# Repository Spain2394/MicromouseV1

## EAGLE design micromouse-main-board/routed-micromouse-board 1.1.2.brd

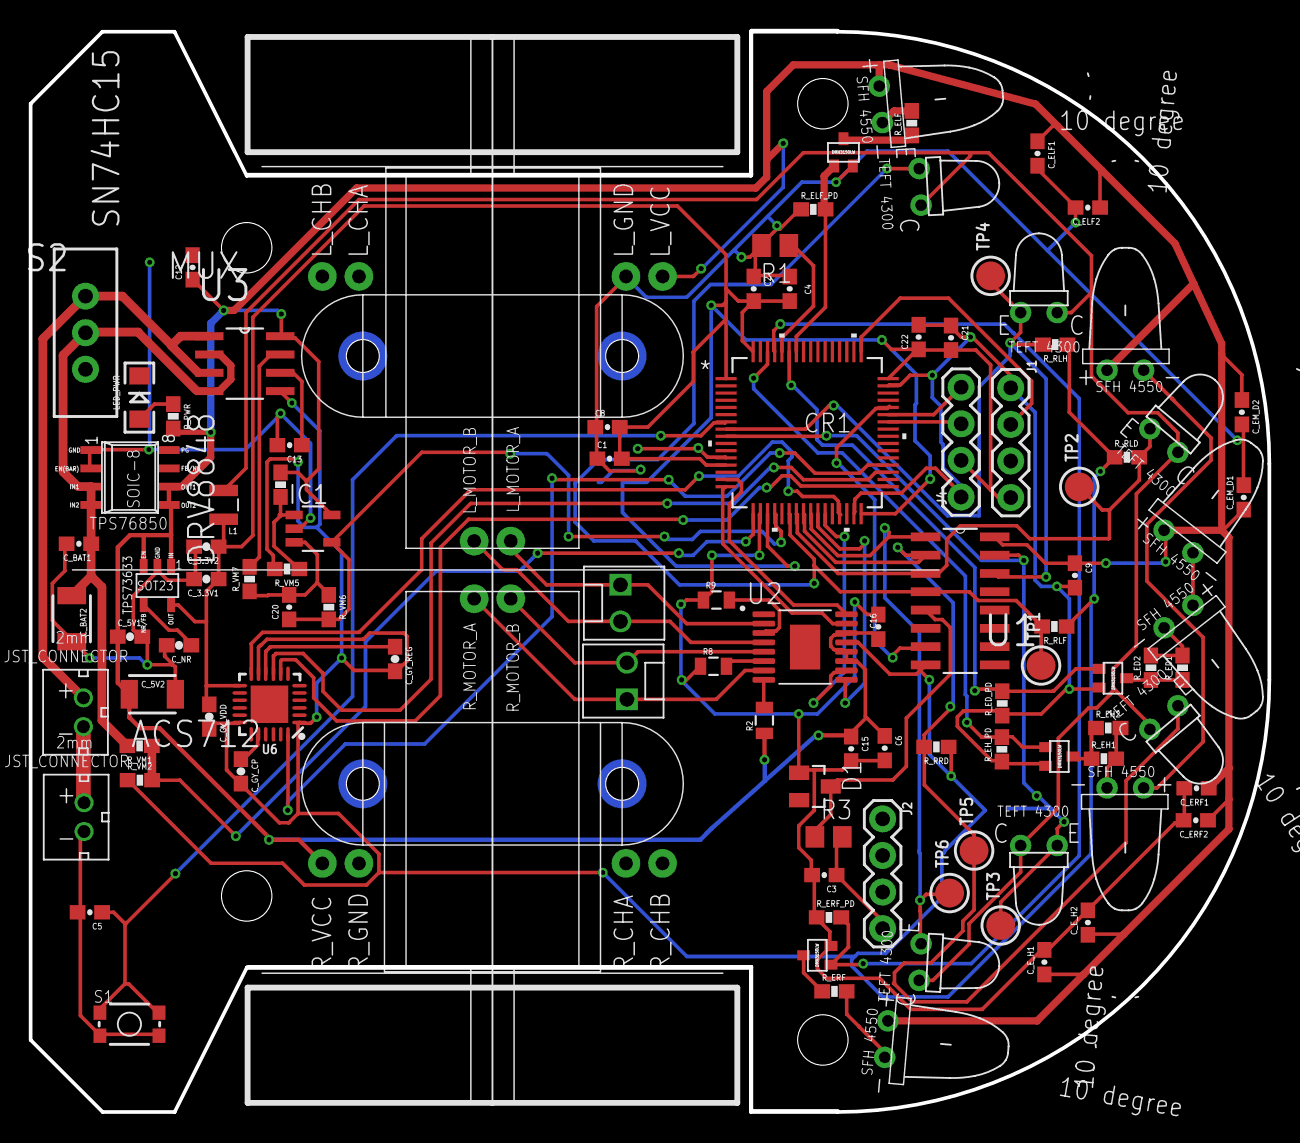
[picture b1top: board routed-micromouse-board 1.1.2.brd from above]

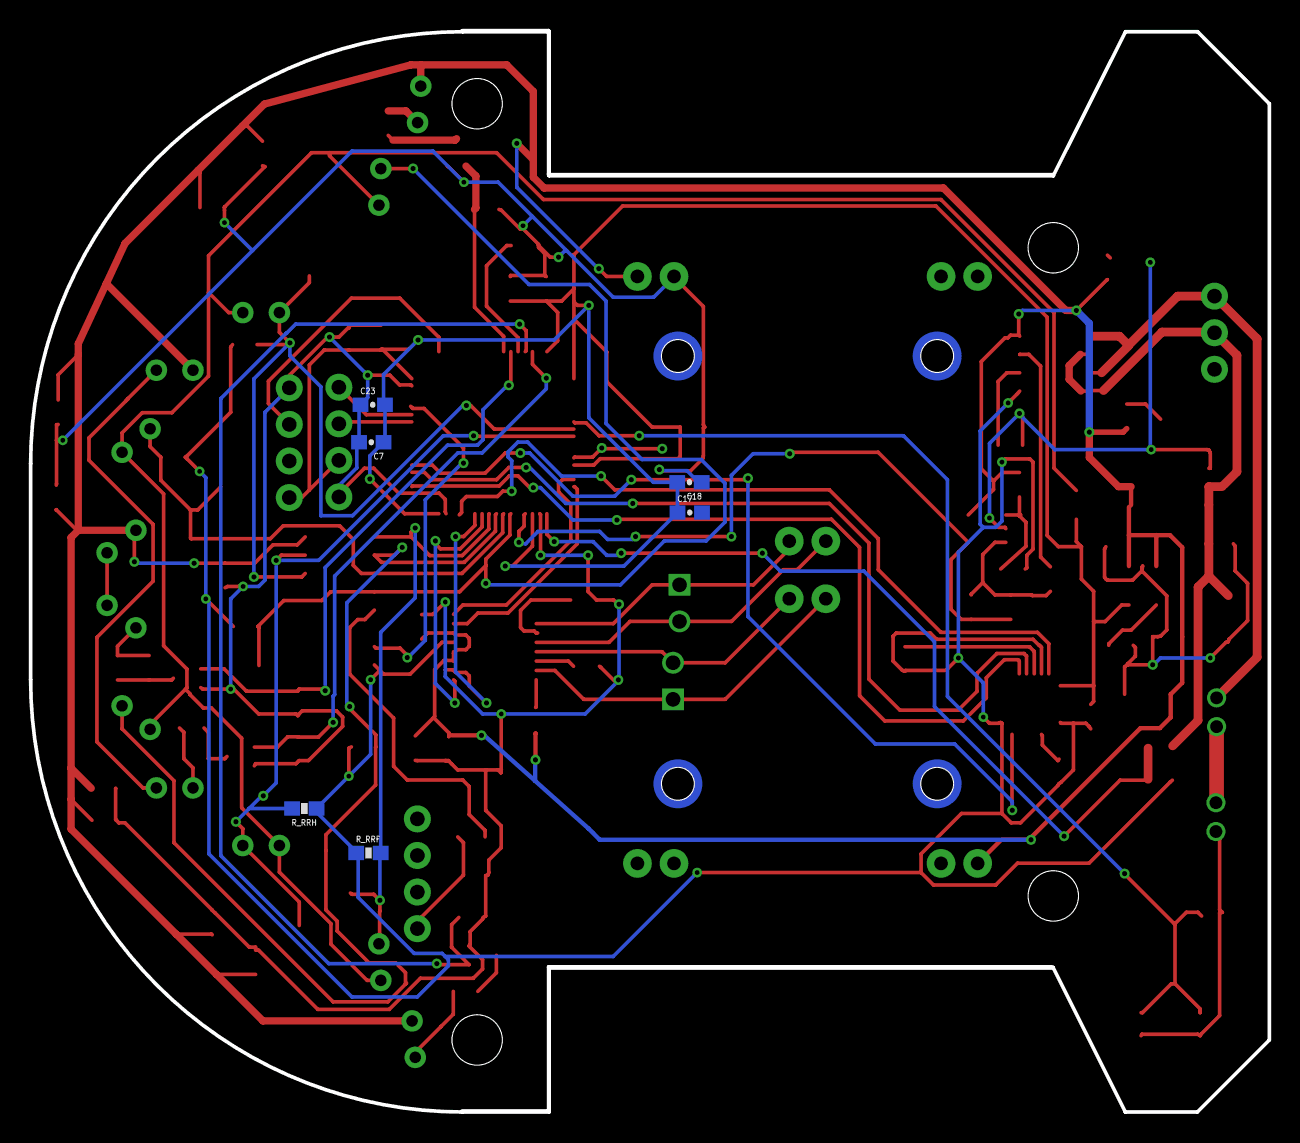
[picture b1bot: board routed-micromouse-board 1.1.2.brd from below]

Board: 2 copper layers, 86.0 x 75.0 mm, 108 parts (6 on the bottom side), 61 nets.

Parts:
C1: 1.1uF; 0603-CAP
C2, C8, C18, C21, C23: 4.7uF; 0603-CAP
C3: 1.4 uF; 0603-CAP
C4, C13: 0.01uF; 0603-CAP
C5, C6, C7, C17, C22: 0.1uF; 0603-CAP
C9, C16: 2.2uF; 0603-CAP
C12: 0.1 uF; 0603-CAP
C15: 10uF; 0603-CAP
C20: 1000pF; 0603-CAP
CR1: STM32F103RET6; LQFP-64
C_3.3V1: 10uF; 0603-CAP
C_3.3V2, C_5V1: 0.1uF; 0603-CAP
C_5V2: 47uF; 1210
C_BAT1: 0.1uF; 0603-CAP
C_BAT2: 47uF; 1210
C_ELF1: 4.7uF; 0603-CAP
C_ELF2: 0.1uF; 0603-CAP
C_EM_D1: 4.7uF; 0603-CAP
C_EM_D2: 0.1uF; 0603-CAP
C_ERF1: 4.7uF; 0603-CAP
C_ERF2: 0.1uF; 0603-CAP
C_E_H1: 4.7uF; 0603-CAP
C_E_H2: 0.1uF; 0603-CAP
C_GY_CP: 2.2nF; 0603-CAP
C_GY_REG: 0.1uF; 0603-CAP
C_GY_VDD: 0.1uF; 0603-CAP
C_NR: 0.1uF; 0603-CAP
D1: SOT23
IC1: LM321MFX; SOT23-5
J1, J2, J4: 1X04
JP1, JP3: MOLEX-1X2
L1: 10uH; 1007
LED_PWR: green; LED-1206
LEFT_FRONT_EMITTER: EMITTER
NMOS1, NMOS2, NMOS3, NMOS4: DMN3150LW
R1: 1k; M0805
R2: 10k; 0805
R3: 1k; R0805
R8, R9: 500m; 0805
REC_LF: RECEIVER
R_ED1, R_ED2: 5.6; 0603-RES
R_ED_PD: 47k; 0603-RES
R_EH1, R_EH2: 5.6; 0603-RES
R_EH_PD: 47k; 0603-RES
R_ELF: 10; 0603-RES
R_ELF_PD: 47k; 0603-RES
R_ERF: 10; 0603-RES
R_ERF_PD: 47k; 0603-RES
R_PWR: 1k; 0603-RES
R_RLD: 1.8k; 0603-RES
R_RLF: 1.8k; 0603-RES
R_RLH: 1.8k; 0603-RES
R_RRD: 1.8k; 0603-RES
R_RRF: 1.8k; 0603-RES
R_RRH: 1.8k; 0603-RES
R_VM1: 75k; 0603-RES
R_VM2: 25k; 0603-RES
R_VM4, R_VM5: 100k; 0603-RES
R_VM6: 3.3k; 0603-RES
R_VM7: 1k; 0603-RES
S1: RESET; TACTILE_SWITCH_SMD_4.6X2.8MM
S2: SWITCH-SPDT
TP1, TP2, TP3, TP4, TP5, TP6: TESTPOINT_ROUND_2MM
U1: SN74HC151DR; SOIC127P600X175-16N
U2: DRV8848PWPR; SOP65P640X120-17N
U3: ACS712ELCTR-20A-T; SOIC127P600X175-8N
U6: MPU-6000; QFN-24-EP
U$1, U$2: JST_CONNECTOR_FEMALE
U$3: TPS73633(SOT-23)
U$4: TPS76850(SOIC-8)
U$7, U$8, U$9, U$20, U$21: RECEIVER
U$11, U$13, U$17, U$18, U$19: EMITTER
U$12: MY_MM_MOTOR_MOUNT

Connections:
3.3V: C1.2, C2.2, C4.2, C7.1, C8.2, C17.1, C18.2, C21.2, C22.1, C23.2, CR1.1, CR1.13, CR1.19, CR1.32, CR1.48, CR1.64, C_3.3V1.1, C_3.3V2.1, C_GY_VDD.1, J1.4, J4.2, L1.1, U6.13, U$3.OUT
5V: C6.1, C9.1, C12.1, C15.1, C16.1, C_5V1.1, C_5V2.1, C_ELF1.1, C_ELF2.1, C_EM_D1.1, C_EM_D2.1, C_ERF1.1, C_ERF2.1, C_E_H1.1, C_E_H2.1, IC1.5, LEFT_FRONT_EMITTER.+, R2.1, R_PWR.2, R_VM4.1, U1.16, U2.11, U2.12, U2.14, U3.8, U$3.EN, U$3.IN, U$4.OUT1, U$4.OUT2, U$11.+, U$12.L_VCC, U$12.R_VCC, U$13.+, U$18.+
(USART1)_RX: CR1.42, J4.3
(USART1)_TX: CR1.43, J4.4
A3.3V: L1.2, REC_LF.C, U$7.C, U$8.C, U$9.C, U$20.C, U$21.C
AGND: C_GY_CP.2, C_GY_REG.2, C_GY_VDD.2, R_RLD.1, R_RLF.1, R_RLH.1, R_RRD.1, R_RRF.1, R_RRH.1, R_VM2.1, R_VM5.2, U1.8, U2.13, U3.5, U6.1, U6.11, U6.18
BATT_CONN: U$1.+, U$2.-
CURRENT_SENSE: C20.1, CR1.20, IC1.4, R_VM6.2
D2_EM: R_ED1.2, R_ED2.2, U$17.-
D_EM: U$11.-, U$17.+
EM_D: CR1.59, NMOS2.G, R_ED_PD.2
EM_H: CR1.62, NMOS4.G, R_EH_PD.2
EM_LF: CR1.58, NMOS1.G, R_ELF_PD.2
EM_RF: CR1.61, NMOS3.G, R_ERF_PD.2
GND: C1.1, C2.1, C3.2, C4.1, C5.2, C6.2, C7.2, C8.1, C9.2, C12.2, C13.2, C15.2, C16.2, C17.2, C18.1, C21.1, C22.2, C23.1, CR1.12, CR1.18, CR1.31, CR1.47, CR1.63, C_3.3V1.2, C_3.3V2.2, C_5V1.2, C_5V2.2, C_BAT1.2, C_BAT2.2, C_ELF1.2, C_ELF2.2, C_EM_D1.2, C_EM_D2.2, C_ERF1.2, C_ERF2.2, C_E_H1.2, C_E_H2.2, C_NR.2, D1.1, IC1.2, J1.1, J4.1, LED_PWR.C, NMOS1.S, NMOS2.S, NMOS3.S, NMOS4.S, R1.2, R8.1, R9.1, R_ED_PD.1, R_EH_PD.1, R_ELF_PD.1, R_ERF_PD.1, S1.1, S1.2, U$1.-, U$3.GND, U$4.EN(BAR), U$4.GND, U$12.L_GND, U$12.R_GND
H2_EM: R_EH1.2, R_EH2.2, U$19.-
H_EM: U$18.-, U$19.+
INT: CR1.29, U6.12
LEFT_MOTOR_H: JP1.1, U2.2, U$12.L_MOTOR_A
LEFT_MOTOR_L: JP1.2, U2.4, U$12.L_MOTOR_B
LF_EM: LEFT_FRONT_EMITTER.-, R_ELF.2
MUX_EN: CR1.44, U1.7
unnamed: C13.1, U3.6
unnamed: D1.3, R3.1, U1.5
unnamed: NMOS3.D, R_ERF.1
unnamed: NMOS1.D, R_ELF.1
unnamed: CR1.60, R1.1
unnamed: R2.2, U2.8
unnamed: R9.2, U2.3
unnamed: NMOS2.D, R_ED1.1, R_ED2.1
unnamed: NMOS4.D, R_EH1.1, R_EH2.1
unnamed: R8.2, U2.6
unnamed: IC1.1, R_VM4.2, R_VM5.1
unnamed: R_VM7.2, U3.7
unnamed: C_NR.1, U$3.NR/FB
unnamed: LED_PWR.A, R_PWR.1
unnamed: C_GY_REG.1, U6.10
unnamed: C_GY_CP.1, U6.20
unnamed: C20.2, IC1.3, R_VM6.1, R_VM7.1
NRST: C5.1, CR1.7, S1.3, S1.4
PWM_MOTOR_1: CR1.15, U2.16
PWM_MOTOR_2: CR1.16, U2.15
PWM_MOTOR_3: CR1.26, U2.9
PWM_MOTOR_4: CR1.27, U2.10
REC_LD: CR1.23, R_RLD.2, TP2.P$1, U1.3, U$7.E
REC_LF: CR1.22, REC_LF.E, R_RLF.2, TP1.P$1, U1.4
REC_LH: CR1.8, R_RLH.2, TP4.P$1, U1.14, U$21.E
REC_RD: CR1.24, R_RRD.2, TP5.P$1, U1.2, U$8.E
REC_RF: CR1.25, R_RRF.2, TP6.P$1, U1.1, U$9.E
REC_RH: CR1.9, R_RRH.2, TP3.P$1, U1.15, U$20.E
RF_EM: R_ERF.2, U$13.-
RIGHT_MOTOR_H: JP3.1, U2.7, U$12.R_MOTOR_A
RIGHT_MOTOR_L: JP3.2, U2.5, U$12.R_MOTOR_B
SENSOR_DEBUG: C3.1, J2.4, R3.2
SPI2_MISO: CR1.35, U6.9
SPI2_MOSI: CR1.36, U6.24
SPI2_NSS: CR1.33, U6.8
SWCLK: CR1.49, J1.2
VBAT_SENSE: CR1.17, R_VM1.1, R_VM2.2
V_BATT: C_BAT1.1, C_BAT2.1, R_VM1.2, S2.2, U3.2, U3.4, U$4.IN1, U$4.IN2
V_BATT_POWER: S2.3, U3.1, U3.3, U$2.+

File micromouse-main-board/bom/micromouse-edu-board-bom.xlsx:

Part | Value | Device | Package | Description | AVAILABILITY | DESCRIPTION | MANUFACTURER_PART_NUMBER | MF | MP | PACKAGE | PRICE | PROD_ID | SF_ID | SPICEPREFIX | VENDOR
C1 | 1.1uF | CAP0603-CAP | 0603-CAP | Capacitor
C2 | 4.7uF | CAP0603-CAP | 0603-CAP | Capacitor
C3 | 1.4 uF | CAP0603-CAP | 0603-CAP | Capacitor
C4 | 0.01uF | CAP0603-CAP | 0603-CAP | Capacitor
C5 | 0.1uF | CAP0603-CAP | 0603-CAP | Capacitor
C6 | 0.1uF | CAP0603-CAP | 0603-CAP | Capacitor
C7 | 0.1uF | CAP0603-CAP | 0603-CAP | Capacitor
C8 | 4.7uF | CAP0603-CAP | 0603-CAP | Capacitor
C9 | 2.2uF | CAP0603-CAP | 0603-CAP | Capacitor
C12 | 0.1 uF | CAP0603-CAP | 0603-CAP | Capacitor
C13 | 0.01uF | CAP0603-CAP | 0603-CAP | Capacitor
C15 | 10uF | CAP0603-CAP | 0603-CAP | Capacitor
C16 | 2.2uF | CAP0603-CAP | 0603-CAP | Capacitor
C17 | 0.1uF | CAP0603-CAP | 0603-CAP | Capacitor
C18 | 4.7uF | CAP0603-CAP | 0603-CAP | Capacitor
C20 | 1000pF | CAP0603-CAP | 0603-CAP | Capacitor
C21 | 4.7uF | CAP0603-CAP | 0603-CAP | Capacitor
C22 | 0.1uF | CAP0603-CAP | 0603-CAP | Capacitor
C23 | 4.7uF | CAP0603-CAP | 0603-CAP | Capacitor
CR1 | STM32F103RET6 | STM32F103RET6 | LQFP-64 |  |  |  | STM32F103RET6 |  |  |  |  |  |  |  | STMicroelectronics
C_3.3V1 | 10uF | CAP0603-CAP | 0603-CAP | Capacitor
C_3.3V2 | 0.1uF | CAP0603-CAP | 0603-CAP | Capacitor
C_5V1 | 0.1uF | CAP0603-CAP | 0603-CAP | Capacitor
C_5V2 | 47uF | CAP1210 | 1210 | Capacitor
C_BAT1 | 0.1uF | CAP0603-CAP | 0603-CAP | Capacitor
C_BAT2 | 47uF | CAP1210 | 1210 | Capacitor
C_ELF1 | 4.7uF | CAP0603-CAP | 0603-CAP | Capacitor
C_ELF2 | 0.1uF | CAP0603-CAP | 0603-CAP | Capacitor
C_EM_D1 | 4.7uF | CAP0603-CAP | 0603-CAP | Capacitor
C_EM_D2 | 0.1uF | CAP0603-CAP | 0603-CAP | Capacitor
C_ERF1 | 4.7uF | CAP0603-CAP | 0603-CAP | Capacitor
C_ERF2 | 0.1uF | CAP0603-CAP | 0603-CAP | Capacitor
C_E_H1 | 4.7uF | CAP0603-CAP | 0603-CAP | Capacitor
C_E_H2 | 0.1uF | CAP0603-CAP | 0603-CAP | Capacitor
C_GY_CP | 2.2nF | CAP0603-CAP | 0603-CAP | Capacitor
C_GY_REG | 0.1uF | CAP0603-CAP | 0603-CAP | Capacitor
C_GY_VDD | 0.1uF | CAP0603-CAP | 0603-CAP | Capacitor
C_NR | 0.1uF | CAP0603-CAP | 0603-CAP | Capacitor
D1 |  | ZENER-DIODESOT23 | SOT23 | Z-Diode
IC1 | LM321MFX | LM321MFX | SOT23-5 | Low Power Single Op Amp
J1 |  | CONN_04 | 1X04 | Multi connection point. Often used as Generic Header-pin footprint for 0.1 inch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 |  |  |  |  |  |  |  | CONN-09696
J2 |  | CONN_04 | 1X04 | Multi connection point. Often used as Generic Header-pin footprint for 0.1 inch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 |  |  |  |  |  |  |  | CONN-09696
J3 | HTSS-103-XX-XX-D | HTSS-103-XX-XX-D | HTSS-103-XX-XX-D | HIGH TEMP TOP SHROUD TERMINAL STRIP.
J4 |  | CONN_04 | 1X04 | Multi connection point. Often used as Generic Header-pin footprint for 0.1 inch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 |  |  |  |  |  |  |  | CONN-09696
J5 | HTSS-103-XX-XX-D | HTSS-103-XX-XX-D | HTSS-103-XX-XX-D | HIGH TEMP TOP SHROUD TERMINAL STRIP.
J6 | HTSS-102-XX-XX-D | HTSS-102-XX-XX-D | HTSS-102-XX-XX-D | HIGH TEMP TOP SHROUD TERMINAL STRIP.
J7 | HTSS-102-XX-XX-D | HTSS-102-XX-XX-D | HTSS-102-XX-XX-D | HIGH TEMP TOP SHROUD TERMINAL STRIP.
JP1 |  | M02POLAR | MOLEX-1X2 | Header 2
JP3 |  | M02POLAR | MOLEX-1X2 | Header 2
L1 | 10uH | INDUCTOR1007 | 1007 | Inductors
LED_PWR | green | LED1206 | LED-1206 | LEDs
LEFT_FRONT_EMITTER | EMITTER | EMITTER | EMITTER
NMOS1 | DMN3150LW | DMN3150LW | DMN3150LW
NMOS2 | DMN3150LW | DMN3150LW | DMN3150LW
NMOS3 | DMN3150LW | DMN3150LW | DMN3150LW
NMOS4 | DMN3150LW | DMN3150LW | DMN3150LW
R1 | 1k | R-US_M0805 | M0805 | RESISTOR
R2 | 10k | RESISTOR0805-RES | 805 | Resistor
R3 | 1k | R-US_R0805 | R0805 | RESISTOR
R8 | 500m | RESISTOR0805-RES | 805 | Resistor
R9 | 500m | RESISTOR0805-RES | 805 | Resistor
REC_LF | RECEIVER | RECEIVER | RECEIVER
R_ED1 | 5.6 | RESISTOR0603-RES | 0603-RES | Resistor
R_ED2 | 5.6 | RESISTOR0603-RES | 0603-RES | Resistor
R_ED_PD | 47k | RESISTOR0603-RES | 0603-RES | Resistor
R_EH1 | 5.6 | RESISTOR0603-RES | 0603-RES | Resistor
R_EH2 | 5.6 | RESISTOR0603-RES | 0603-RES | Resistor
R_EH_PD | 47k | RESISTOR0603-RES | 0603-RES | Resistor
R_ELF | 10 | RESISTOR0603-RES | 0603-RES | Resistor
R_ELF_PD | 47k | RESISTOR0603-RES | 0603-RES | Resistor
R_ERF | 10 | RESISTOR0603-RES | 0603-RES | Resistor
R_ERF_PD | 47k | RESISTOR0603-RES | 0603-RES | Resistor
R_PWR | 1k | RESISTOR0603-RES | 0603-RES | Resistor
R_RLD | 1.8k | RESISTOR0603-RES | 0603-RES | Resistor
R_RLF | 1.8k | RESISTOR0603-RES | 0603-RES | Resistor
R_RLH | 1.8k | RESISTOR0603-RES | 0603-RES | Resistor
R_RRD | 1.8k | RESISTOR0603-RES | 0603-RES | Resistor
R_RRF | 1.8k | RESISTOR0603-RES | 0603-RES | Resistor
R_RRH | 1.8k | RESISTOR0603-RES | 0603-RES | Resistor
R_VM1 | 75k | RESISTOR0603-RES | 0603-RES | Resistor
R_VM2 | 25k | RESISTOR0603-RES | 0603-RES | Resistor
R_VM4 | 100k | RESISTOR0603-RES | 0603-RES | Resistor
R_VM5 | 100k | RESISTOR0603-RES | 0603-RES | Resistor
R_VM6 | 3.3k | RESISTOR0603-RES | 0603-RES | Resistor
R_VM7 | 1k | RESISTOR0603-RES | 0603-RES | Resistor
S1 | RESET | SWITCH-MOMENTARY-2SMD-4.6X2.8MM | TACTILE_SWITCH_SMD_4.6X2.8MM | Various NO switches- pushbuttons
S2 |  | SWITCH-SPSTPTH | SWITCH-SPDT | SPST Switch
TP1 |  | TESTPOINTROUND2MM | TESTPOINT_ROUND_2MM | Test Point
TP2 |  | TESTPOINTROUND2MM | TESTPOINT_ROUND_2MM | Test Point
TP3 |  | TESTPOINTROUND2MM | TESTPOINT_ROUND_2MM | Test Point
TP4 |  | TESTPOINTROUND2MM | TESTPOINT_ROUND_2MM | Test Point
TP5 |  | TESTPOINTROUND2MM | TESTPOINT_ROUND_2MM | Test Point
TP6 |  | TESTPOINTROUND2MM | TESTPOINT_ROUND_2MM | Test Point
U$1 | JST_CONNECTOR_FEMALE | JST_CONNECTOR_FEMALE | JST_CONNECTOR_FEMALE
U$2 | JST_CONNECTOR_FEMALE | JST_CONNECTOR_FEMALE | JST_CONNECTOR_FEMALE
U$3 | TPS73633(SOT-23) | TPS73633(SOT-23) | TPS73633(SOT-23)
U$4 | TPS76850(SOIC-8) | TPS76850(SOIC-8) | TPS76850(SOIC-8)
U$7 | RECEIVER | RECEIVER | RECEIVER
U$8 | RECEIVER | RECEIVER | RECEIVER
U$9 | RECEIVER | RECEIVER | RECEIVER
U$11 | EMITTER | EMITTER | EMITTER
U$12 | MY_MM_MOTOR_MOUNT | MY_MM_MOTOR_MOUNT | MY_MM_MOTOR_MOUNT
U$13 | EMITTER | EMITTER | EMITTER
U$17 | EMITTER | EMITTER | EMITTER
U$18 | EMITTER | EMITTER | EMITTER
U$19 | EMITTER | EMITTER | EMITTER
U$20 | RECEIVER | RECEIVER | RECEIVER
U$21 | RECEIVER | RECEIVER | RECEIVER
U1 | SN74HC151DR | SN74HC151DR | SOIC127P600X175-16N | 8-Line to 1-Line Dataselectors /MultiPlexers | Unavailable | 8-Line To 1-Line Data Selectors/Multiplexers 16-SOIC -40 to 85 |  | Texas Instruments | SN74HC151DR | SOIC-16 Texas Instruments | None
U2 | DRV8848PWPR | DRV8848PWPR | SOP65P640X120-17N | None | Unavailable | 2A Dual H-Bridge Motor Driver _PWM Control_ 16-HTSSOP -40 to 85 |  | Texas Instruments | DRV8848PWPR | HTSSOP-16 Texas Instruments | None
U3 | ACS712ELCTR-20A-T | ACS712ELCTR-20A-T | SOIC127P600X175-8N | Linear Current Sensor | Unavailable | Fully Integrated
U6 | MPU-6000 | MPU-6000 | QFN-24-EP | Invensense MPU-6000 6-Axis Gryoscope/Accelerometer |  |  |  |  |  |  |  | IC-11089 | SEN-11234
X1 | RASPI_GPIO_B+#_PIN | RASPI_GPIO_B+#_PIN | RASPI_GPIO_B+_PIN | 2x20 header connector

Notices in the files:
parts and their libraries:
SparkFun-Electromechanical: Licensing: Creative Commons ShareAlike 4.0 International - https://creativecommons.org/licenses/by-sa/4.0
SparkFun: Licensing: CC v3.0 Share-Alike You are welcome to use this library for commercial purposes.
